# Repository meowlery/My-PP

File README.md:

# My PP

“My PP” is a macropad that I designed with 9 keys. PP stands for “Personal Pad,” since it has my personal features that I use most. You probably noticed that it’s a reference to “PC,” which stands for “Personal Computer” (; (i know it's very random).

## Notes:

I built this macropad using a Hack Club tutorial, and it was really fun. Here is how the final product will look like after building the parts together:

## Challenges:

With designing this macropad, I learned many things, which was really cool. For example, I designed a PCB for the first time! I already have an Arduino with a breadboard for some small projects, and I wondered many times about how to design a PCB but thought it was way more difficult than it actually is. And I created for the first time something in 3D with Fusion360.

## Programs I used:

- Fusion360 for CAD
- KiCad for the PCB
- QMK Firmware for the firmware (did I need to explain it?)

### BOM:

Here are the things that are inside my macropad:

- 4x M3 Heatset
- 4x M3x16 Bolt
- 4x Blank DSA Keycaps
- 1x XIAO RP2040
- 2x SK6812 MINI Leds
- 9x Cherry MX Switches

### PCB:

### Schematic:

### Case:

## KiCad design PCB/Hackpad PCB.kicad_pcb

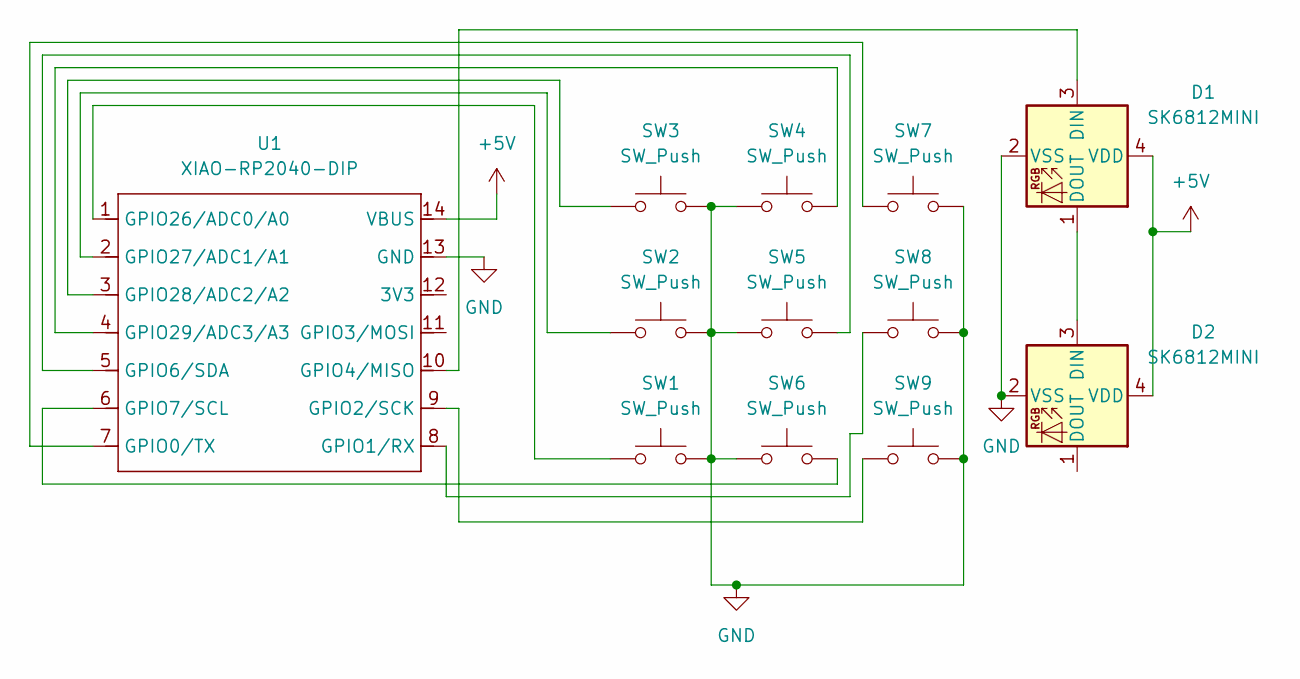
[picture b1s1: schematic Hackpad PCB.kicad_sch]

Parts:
D1, D2: SK6812MINI; LED_SK6812MINI_PLCC4_3.5x3.5mm_P1.75mm
SW1, SW2, SW3, SW4, SW5, SW6, SW7, SW8, SW9: SW_Push; SW_Cherry_MX_1.00u_PCB
U1: XIAO-RP2040-DIP

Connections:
+5V: D1.4 (VDD), D2.4 (VDD), U1.14 (VBUS)
GND: D1.2 (VSS), D2.2 (VSS), SW1.2, SW2.2, SW3.2, SW4.1, SW5.1, SW6.1, SW7.2, SW8.2, SW9.2, U1.13 (GND)
unnamed: D1.3 (DIN), U1.10 (GPIO4/MISO)
unnamed: D1.1 (DOUT), D2.3 (DIN)
unnamed: SW7.1, U1.7 (GPIO0/TX)
unnamed: SW8.1, U1.8 (GPIO1/RX)
unnamed: SW9.1, U1.9 (GPIO2/SCK)
unnamed: SW5.2, U1.5 (GPIO6/SDA)
unnamed: SW6.2, U1.6 (GPIO7/SCL)
unnamed: SW1.1, U1.1 (GPIO26/ADC0/A0)
unnamed: SW2.1, U1.2 (GPIO27/ADC1/A1)
unnamed: SW3.1, U1.3 (GPIO28/ADC2/A2)
unnamed: SW4.2, U1.4 (GPIO29/ADC3/A3)

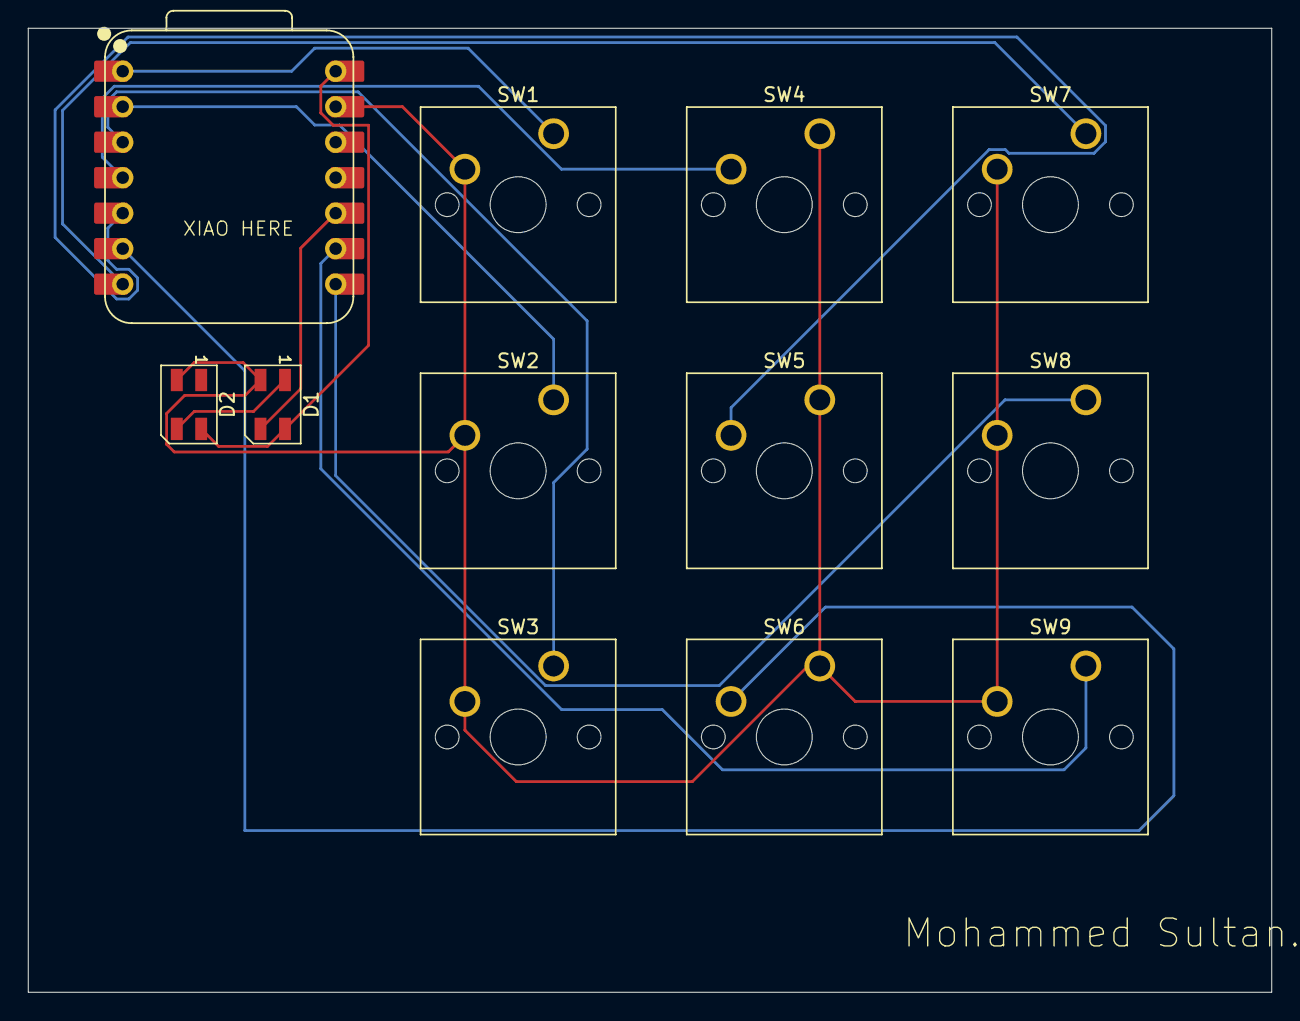
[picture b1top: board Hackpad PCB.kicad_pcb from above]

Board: 2 copper layers, 89.0 x 69.0 mm, 12 parts (0 on the bottom side), 13 nets.

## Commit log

2025-12-28 Revise README with project details and BOM
    Updated the README to provide detailed information about the macropad, including its features, challenges faced during the build, and a bill of materials.
2025-12-28 Create a
2025-12-28 Revise challenges section in README
    Updated the README to clarify challenges faced during the project.
2025-12-29 Enhance README with project details and image
    Updated README.md to include final product image and details about the design process.
2025-12-29 Add additional image to Case section
    Added a new image to the Case section of the README.
2025-12-29 Fix grammar and punctuation in README.md
    Corrected punctuation and grammar in the README.
